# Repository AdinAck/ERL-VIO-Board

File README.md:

# ERL-VIO-Board
A small board intended for cleaning up the VIO sets, providing power options, and connecting the cameras and IMU.

# **WARNING**

**v1.0 has a silk screen error for the external supply port. - should be + and + should be -**

## Project Goal
Make it as easy and fast as possible to swap out cameras or IMU, and to diagnose problems.

## Features
- Verbose connectivity for IMU and cameras
- USB to UART bridge for IMU
- `SYNC` connection between IMU and cameras
- Optional external supply for cameras

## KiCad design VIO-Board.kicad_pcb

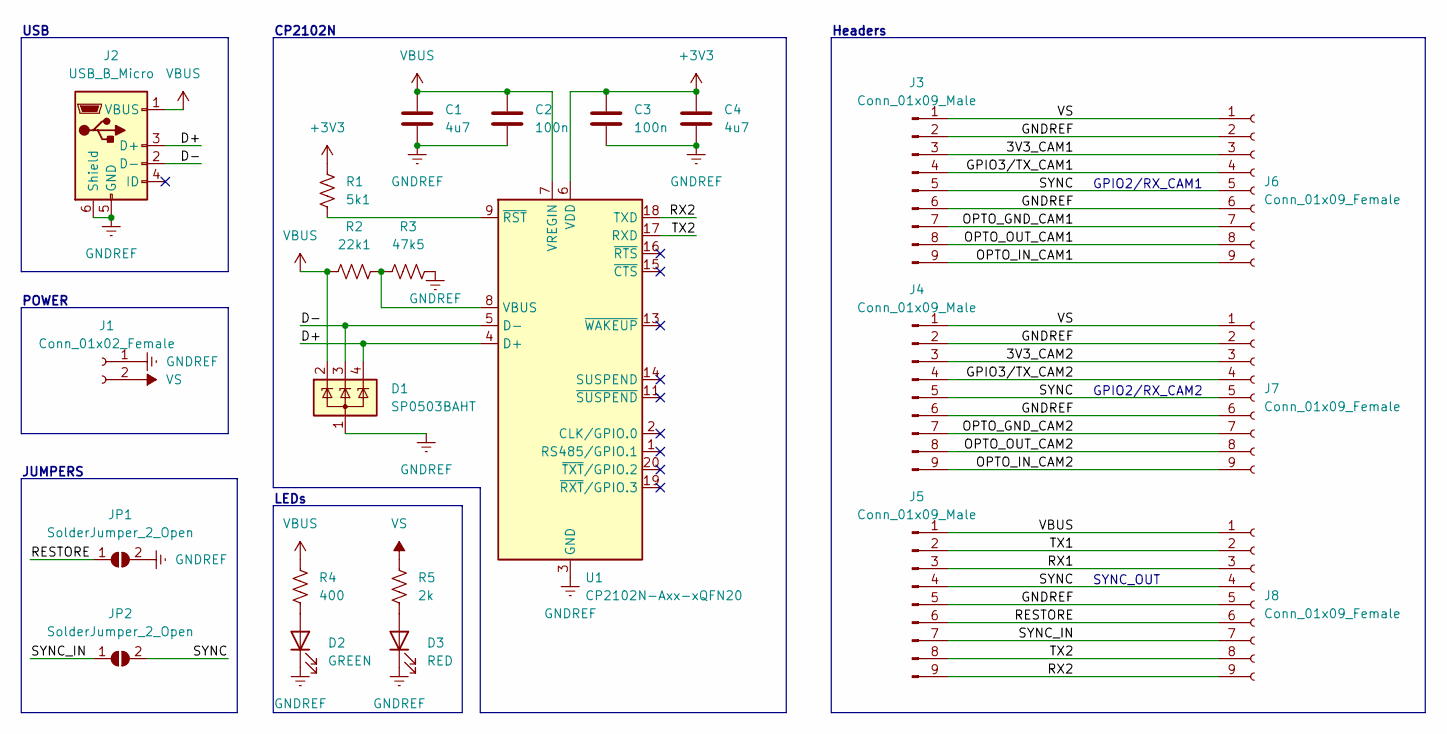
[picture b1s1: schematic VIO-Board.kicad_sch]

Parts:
C1, C4: 4u7; C_0402_1005Metric
C2, C3: 100n; C_0402_1005Metric
D1: SP0503BAHT; SOT-143
D2: GREEN; LED_0603_1608Metric
D3: RED; LED_0603_1608Metric
J1: Conn_01x02_Female; AMASS_XT30U-F_1x02_P5.0mm_Vertical
J2: USB_B_Micro; USB_Micro-B_Molex_47346-0001
J3, J4, J5: Conn_01x09_Male; PinHeader_1x09_P2.54mm_Vertical
J6, J7, J8: Conn_01x09_Female; PinSocket_1x09_P2.54mm_Vertical
JP1, JP2: SolderJumper_2_Open; SolderJumper-2_P1.3mm_Open_RoundedPad1.0x1.5mm
R1: 5k1; R_0402_1005Metric
R2: 22k1; R_0402_1005Metric
R3: 47k5; R_0402_1005Metric
R4: 400; R_0402_1005Metric
R5: 2k; R_0402_1005Metric
U1: CP2102N-Axx-xQFN20; SiliconLabs_QFN-20-1EP_3x3mm_P0.5mm_EP1.8x1.8mm

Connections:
+3V3: C3.1, C4.1, R1.1, U1.6 (VDD)
/3V3_CAM1: J3.3, J6.3
/3V3_CAM2: J4.3, J7.3
/D+: D1.4 (K), J2.3 (D+), U1.4 (D+)
/D-: D1.3 (K), J2.2 (D-), U1.5 (D-)
/GPIO3/TX_CAM1: J3.4, J6.4
/GPIO3/TX_CAM2: J4.4, J7.4
/OPTO_GND_CAM1: J3.7, J6.7
/OPTO_GND_CAM2: J4.7, J7.7
/OPTO_IN_CAM1: J3.9, J6.9
/OPTO_IN_CAM2: J4.9, J7.9
/OPTO_OUT_CAM1: J3.8, J6.8
/OPTO_OUT_CAM2: J4.8, J7.8
/RESTORE: J5.6, J8.6, JP1.1 (A)
/RX1: J5.3, J8.3
/RX2: J5.9, J8.9, U1.18 (TXD)
/SYNC: J3.5, J4.5, J5.4, J6.5, J7.5, J8.4, JP2.2 (B)
/SYNC_IN: J5.7, J8.7, JP2.1 (A)
/TX1: J5.2, J8.2
/TX2: J5.8, J8.8, U1.17 (RXD)
GNDREF: C1.2, C2.2, C3.2, C4.2, D1.1 (A), D2.1 (K), D3.1 (K), J1.1, J2.5 (GND), J2.6 (Shield), J3.2, J3.6, J4.2, J4.6, J5.5, J6.2, J6.6, J7.2, J7.6, J8.5, JP1.2 (B), R3.2, U1.3 (GND), U1.12 (GND), U1.21 (GND)
unnamed: D2.2 (A), R4.2
unnamed: D3.2 (A), R5.2
unnamed: R1.2, U1.9 (~RST)
unnamed: R2.2, R3.1, U1.8 (VBUS)
VBUS: C1.1, C2.1, D1.2 (K), J2.1 (VBUS), J5.1, J8.1, R2.1, R4.1, U1.7 (VREGIN)
VS: J1.2, J3.1, J4.1, J6.1, J7.1, R5.1

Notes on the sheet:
Headers
POWER
SYNC_OUT
JUMPERS
GPIO2/RX_CAM2
LEDs
USB
GPIO2/RX_CAM1
CP2102N

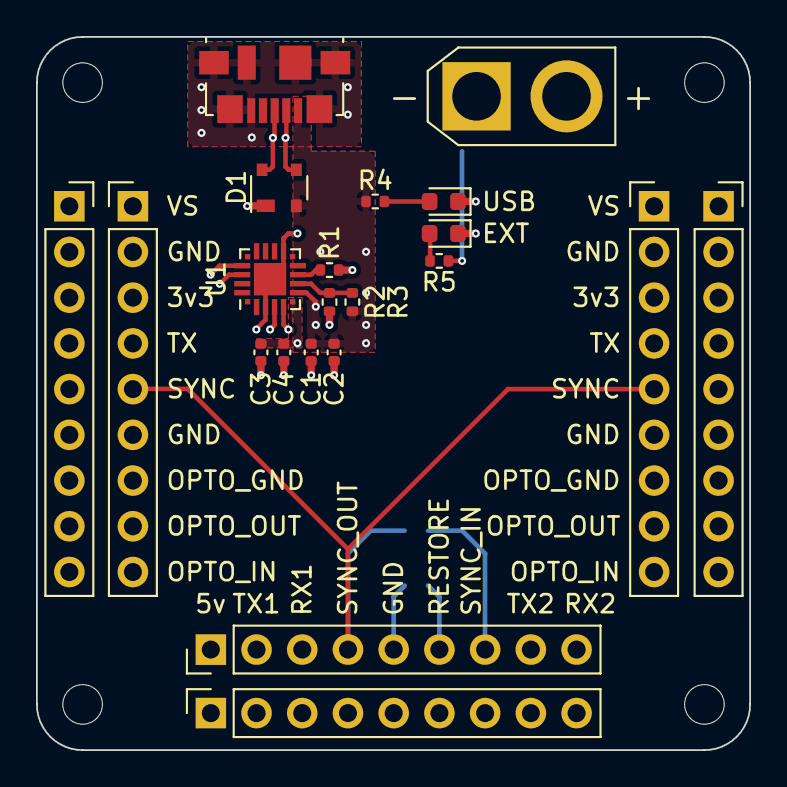
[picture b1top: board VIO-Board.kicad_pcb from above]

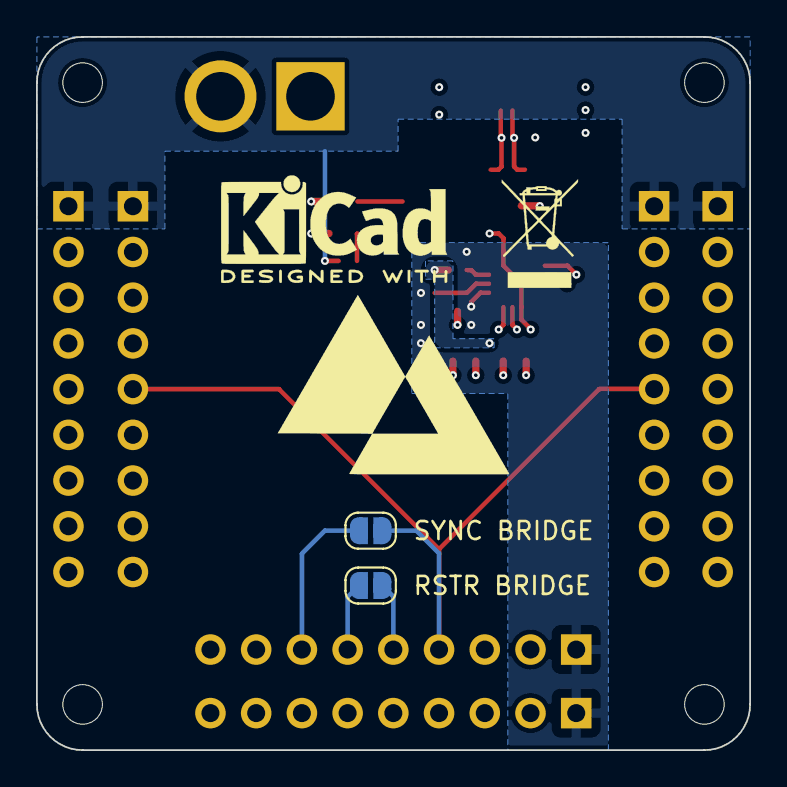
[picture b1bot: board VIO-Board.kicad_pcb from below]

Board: 4 copper layers, 39.6 x 39.6 mm, 23 parts (2 on the bottom side), 27 nets.

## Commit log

2022-05-02 workin
2022-05-06 workin...
2022-05-06 add led
2022-05-06 connectors
2022-05-06 add led again
2022-06-17 new package, ESD protection, fixes
2022-06-17 final touches
2022-06-17 BOM and corrections
2022-06-17 gerber files, small correction
2022-06-17 no need for lib
2022-07-11 readme
2022-08-24 v2.0
